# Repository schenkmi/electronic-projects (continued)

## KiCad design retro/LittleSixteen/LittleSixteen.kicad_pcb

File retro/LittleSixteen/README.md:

# LittleSixteen

LittleSixteen is an Open Hardware remake of the Commodore 16, 116 and Plus/4 home computers, featuring many improvements over the original design.

## Summary
While this project started as a simple redrawing of the C16 schematics, it has now evolved into what could be considered the flagship member of the 264 family of Commodore computers, since it has all the characteristics of the other models [^nospeech] and bears a full array of extra features and improvements, while keeping full compatibility with them.

The new goal of this project is to allow anyone to build a very significant home computer from the '80s from scratch, only using parts that can be found on the market [^almost]. The design is fully through-hole so no particular soldering skills are required for the assembly. The estimated cost of ALL materials (case and power supply included) for a single complete machine is around 250-300€.

## Differences and Improvements
The original Commodore 16 was the victim of several cost-cutting measures during its design phase. Its target price was $99 and Commodore still had to have some margin on that, so they really had to spare every cent they could and they went as far as not mounting the decoupling capacitors for a few chips which happened to have another one "close enough". Thus, a further goal of this project was to undo all of those measures and make the design as clean as possible, while also improving on it.

### Modifications introduced in V4
The goal of V4 was to make LittleSixteen an improved Plus/4 clone, rather than a C16 clone.

- 100% Plus/4 compatible User Port.
- 512 kB Hannes-style RAM expansion (which can be reduced to 256 kB through a single jumper for compatibility reasons).
- 2 ROM banks, each of which can carry the whole set of ROMs: KERNAL + BASIC + Function ROMs.
- Onboard SID (either 6581 or 8580 + Optional Digifix) + 3rd joystick port (SID audio is mixed with the TED/Ext audio with configurable volume but direct dedicated output is also available).
- Direct TED audio output connector.
- Joystick swapper.
- Ability to replace keyboard MOS 6529 with 74x273 (so that 6529 can be recycled for User Port, but that one as well can be replaced with a 74x654).
- Removed FB13 in order to reduce luma/chroma crosstalk and improve video quality.
- Pin header with all tape signals (think Internal Tapuino).
- Pin header with all IEC signals (think Internal SD2IEC).

### Modifications introduced in V3
In V3 we started making improvements to the board. The reasoning behind every modification is detailed on the [Development Blog](https://hackaday.io/project/182543-littlesixteen-commodore-16-mainboard), so I'll be pretty terse here.

- Switched to external power regulation, using the C64 power circuit and power supply: drastically reduces the heat inside the case, which is one of the main CPU/TED failure causes.
- Added current-limiting resistors on all ports exposing power pins: this will avoid short-circuiting the power supply, whatever you do on the external connectors.
- Added internal Joystick port buffers: this is basically like having two [OpenC16JoyAdapter](https://github.com/SukkoPera/OpenC16JoyAdapter)s built into the machine, preventing the TED pins to be directly exposed on the joystick ports, which is another common cause of TED failures. It also gives the ports a fixed ground, allowing the use of "advanced" joysticks with autofire functionalities for instance, which require power from the machine.
- Joystick ports now use DB-9 (more properly: DE-9) connectors, just like any other machine of the era: you can now use your favourite C64/Amiga joystick on your C16.
- Similarly, the Datassette port was changed to the C64-style edge connector. An adapter to keep connecting the 1531 Datassette is trivial to make.
- Moved to the C64 power switch, since this can still be found on the market and is functionally equivalent.
- The CPU can now either be an original 7501/8501 or even a 6510, thanks to [Andrew Challis's adapter](http://hackjunk.com/2017/06/23/commodore-16-plus-4-8501-to-6510-cpu-conversion/) being integrated on the board.
- In a similar fashion, the board can either directly accept an original MOS 251641 PLA or [Daniël Mantione's GAL16V8-based reimplementation](https://www.freepascal.org/~daniel/c16pla/).
- The design flaw that prevented the usage of cartridge-based RAM expansions was fixed: you can now plug in an [OpenC16RamExpansion](https://github.com/SukkoPera/OpenC16RamExpansion) without the internal RAM fighting with it.
- Actually that might not even be necessary, as the board now directly supports either 16 or 64 kB of internal RAM.
- Since the RF modulator is basically useless these days, a [replacement circuit](https://github.com/mbarszcz-pcb/c64-rf-modulator-replacement) was integrated on the board, providing either Luma+Chroma (say S-Video) or Composite Video.
- Added the possibility of combining the KERNAL and BASIC in a single all-in-one ROM: this allows replacing the original power-hungry chips with a single W27C512, which can also incorporate the Plus/4 function ROMs.
- ESD protection was improved on all ports.
- The track and ground plane layout were optimized in a few places in order to reduce noise and crosstalk.

While the comprehensive switch of connectors to the C64 counterparts might be frowned upon, it was done because [C64-style cases](https://icomp.de/shop-icomp/en/shop/product/c64c-case.html) are still in production and this way LittleSixteen V3 will fit them just perfectly, yielding the ability to build new C16s from scratch, which is another one of our goals.

### Modifications introduced in V2
V2 was meant to be a 1:1 copy of the original board with some essential improvements requiring minimum effort. The goal was to have a proved-working design we could start from in order to make improvements.

- The original board was probably laid out by hand and a lot of tracks were drawn with arbitrary slopes. I have sticked to only 45 degrees tracks, which of course means I could not follow the original tracks exactly, but I tried to stay as close to them as possible and to keep all the "visual hints" that allow identifying a track quickly. I must admit I'm quite satisfied of the end result, to be honest.
- I used my usual track widths and via sizes (plus some new values for the larger tracks), I didn't bother figuring out what sizes the original board used.
- All tracks were laid out "by eye", which means with *reasonable* - not *maniacal* - accuracy to the original design. Most care was taken in the positioning of components that ought to be in a certain position (i.e.: screw holes and I/O connectors), to ensure drop-in replaceability. Other components and tracks are "more or less" there, but as the board was wholly laid out from scratch by hand, don't expect sub-millimeter accuracy.
- The footprints for all DIP chips use "long pads". This makes them easier to solder and more solid to the board should you need to rework them. This forced a few tracks running very close to the original pads to be slightly offset away.
- Some footprints are slightly longer/larger/wider pitch/whatever than the originals, so that I could use ready-made KiCad libraries.
- Footprints for the connectors and modulator were taken from [StormTrooper's Plus/4 remake](https://github.com/StormTrooper/Commodore-Plus4), without checking them for correctness.
- I didn't bother to create the right footprint for the original power connector, as there's no point in wasting time for some item that is nowhere to be found these days. I used a much more common one instead. Same goes for the inductor.
- I didn't pay much attention to the silkscreen, many labels can probably be placed better, but I added a description for every IC, like it or not.
- Proper footprints were added for all the protection diodes that Commodore forcibly retrofitted on real boards (See D96-99).
- With the C16, Commodore went as far as saving a few cents by not mounting the decoupling capacitors for a few chips. They left the pads on the board but removed all silkscreen indications. These were restored and assigned random numbers.
- The ground fill is autogenerated by KiCad, so it won't match the original exactly (not even close).
- Probably there's something more I've forgotten.

If you don't like any of the above, feel free to fix it yourself and [submit a Pull Request](https://github.com/SukkoPera/LittleSixteen/pulls).

## Testing
V3  and V4 of the board were throughly tested by project collaborator Edoardo Auteri, as you can read on the [Development Blog](https://hackaday.io/project/182543/log/202804-how-to-make-the-changes-that-change-everything). In his words:

> The machine works flawlessly providing superior audio and video performance, low power consumption and compatibility with the 1530 Datassette Unit (C2N model), SD2IEC, Atari joysticks and pads.

## Assembly
If you want to build your own board, **please make sure read the assembly notes on [the Wiki](https://github.com/SukkoPera/LittleSixteen/wiki) carefully!**

Note that there are different pages for different revisions of the board.

## Releases
If you want to get this board produced, you are recommended to get [the latest release](https://github.com/SukkoPera/LittleSixteen/releases) rather than the current git version, as the latter might be under development and is not guaranteed to be working.

Every release is accompanied by its Bill Of Materials (BOM) file and any relevant notes about it, which you are recommended to read carefully.

**I am not providing ready-to-use gerber files**. If all you want is **to get boards made, I would really appreciate if you did so [in a way that supports the project](#support-the-project)**.

## License
The LittleSixteen documentation, including the design itself, is copyright &copy; SukkoPera 2019-2025 and is licensed under the [Creative Commons Attribution-NonCommercial-ShareAlike 4.0 International License](https://creativecommons.org/licenses/by-nc-sa/4.0/).

This documentation is distributed *as is* and WITHOUT ANY EXPRESS OR IMPLIED WARRANTIES whatsoever with respect to its functionality, operability or use, including, without limitation, any implied warranties OF MERCHANTABILITY, SATISFACTORY QUALITY, FITNESS FOR A PARTICULAR PURPOSE or infringement. We expressly disclaim any liability whatsoever for any direct, indirect, consequential, incidental or special damages, including, without limitation, lost revenues, lost profits, losses resulting from business interruption or loss of data, regardless of the form of action or legal theory under which the liability may be asserted, even if advised of the possibility or likelihood of such damages.

## Support the Project
If you want to get some boards manufactured, you can get them from PCBWay through this link:

You get my gratitude and cheap, professionally-made and good quality PCBs, I get some credit that will help with this and [other projects](https://www.pcbway.com/project/member/shareproject/?bmbid=41100). You won't even have to worry about the various PCB options, it's all pre-configured for you!

Also, if you still have to register, [you can use this link](https://www.pcbway.com/setinvite.aspx?inviteid=41100) to get some bonus initial credit (and yield me some more).

You can also buy me a coffee if you want:

## Thanks
- My father, for buying me my C16 when I was 8, my first computer ever. This project is dedicated to his memory.
- Amiwell, for giving me a free C16 that I used to trace a lot of connections.
- [StormTrooper](https://github.com/StormTrooper/Commodore-Plus4) for his similar project about the Plus/4, which is where many of the footprints and 3D models used in this project come from.
- J. F. Gomez, for the [3D model of the Barrel jack](https://grabcad.com/library/dc-power-jack-5-5mm-x-2-1mm-2-54mm-pitch-1).
- [Edoardo Auteri](https://github.com/kinmami), for his invaluable advice on analog stuff and for fully assembling the first prototype and testing it thoroughly.
- Gordon Fecyk AKA Great White Retro, for beta-testing, making videos of his builds and spreading the word.
- Last but not least, thanks to [PCBWay](https://www.pcbway.com) for sponsoring the project and providing us with free prototypes of V3.

[^nospeech]: Ok, ok... No V364 speech support, I'll admit!
[^almost]: Almost, the CPU, TED and Expansion port connector must be recovered somehow.

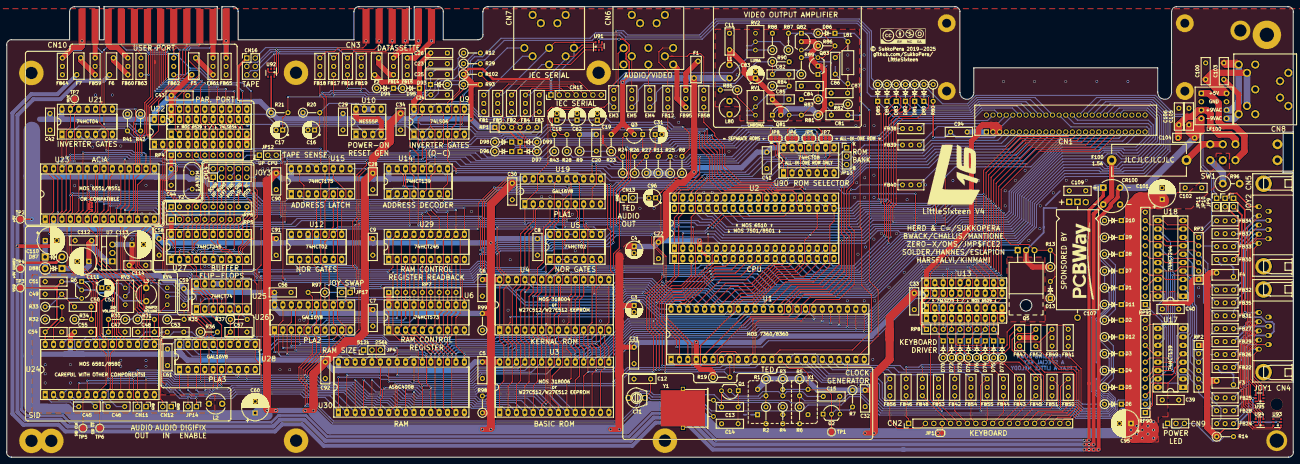
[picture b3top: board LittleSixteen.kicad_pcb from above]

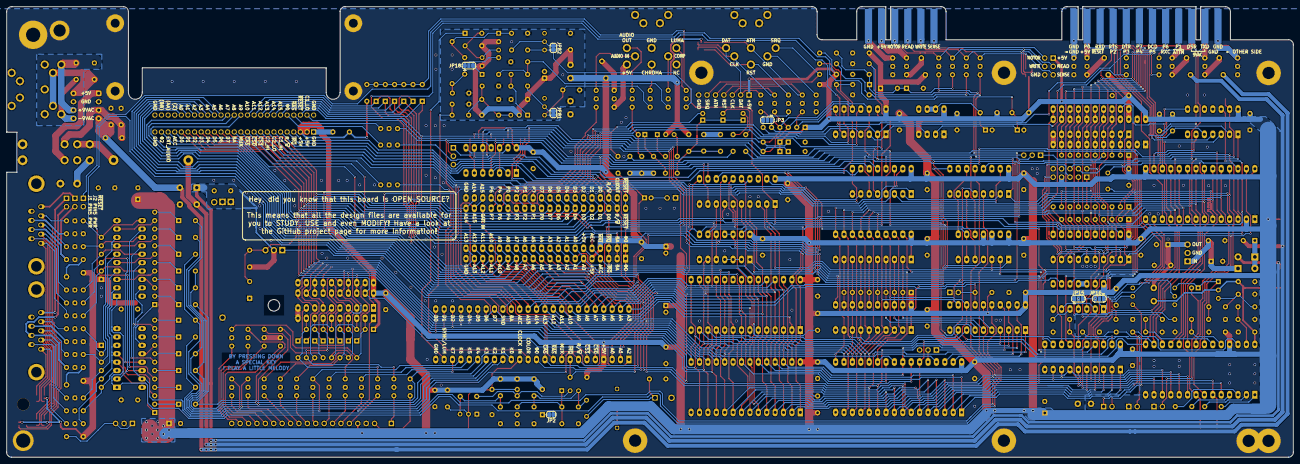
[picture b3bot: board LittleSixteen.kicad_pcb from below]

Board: 2 copper layers, 389.0 x 136.2 mm, 364 parts (7 on the bottom side), 346 nets.

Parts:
C3, C4, C16, C18, C19, C31, C52, C62, C83, C96: 10u/25V; CP_Radial_D5.0mm_P2.00mm
C5, C6, C7, C8, C9, C11, C21, C22, C26, C28, C29, C30, C33, C34, C39, C40, C41, C42, C43, C44, C51, C53, C54, C55, C56, C58, C59, C61, C85, C90, C91, C92, C94, C100, C102, C109, C112, C114: 100n; C_Disc_D8.0mm_W2.5mm_P5.00mm
C12: 22p; C_Disc_D8.0mm_W2.5mm_P5.00mm
C13, C86: 220p; C_Disc_D8.0mm_W2.5mm_P5.00mm
C14, C82: 150p; C_Disc_D8.0mm_W2.5mm_P5.00mm
C15, C20: 10n; C_Disc_D8.0mm_W2.5mm_P5.00mm
C17: 1u/16V; CP_Radial_D5.0mm_P2.00mm
C23, C24, C25, C50, C57: 470p; C_Disc_D8.0mm_W2.5mm_P5.00mm
C32, C84: 100p; C_Disc_D8.0mm_W2.5mm_P5.00mm
C45, C46: 22n; C_Disc_D8.0mm_W2.5mm_P5.00mm
C47, C48: 2.2n; C_Disc_D8.0mm_W2.5mm_P5.00mm
C49: 1n; C_Disc_D8.0mm_W2.5mm_P5.00mm
C60, C95, C101, C110, C111, C113: 470u/25V; CP_Radial_D8.0mm_P3.50mm
C81, C87: 330p; C_Disc_D8.0mm_W2.5mm_P5.00mm
C103, C104, C105, C106: 220n/25V; C_Disc_D8.0mm_W2.5mm_P5.00mm
C107: 2200u/25V; Axial_Cap_Dual
CN1: EXPANSION_CONNECTOR; 50Pin_Edge_Connector
CN2: KEYBOARD_HEADER; PinHeader_1x20_P2.54mm_NoPin2
CN4: JOY1; DB_9M
CN5: JOY2; DB_9M
CN6: AUDIO_VIDEO; DIN-8_DS_8_102_OR_102B
CN7: SERIAL_BUS; DIN-6_DS_6_102_OR_102B
CN8: POWER_INPUT; DIN-7_DS_7_102_OR_102B
CN9: LED_CONNECTOR; PinHeader_1x03_P2.54mm_Vertical
CN10: USERPORT; Plus4_UserPort
CN11: CONN_SID_OUTPUT; PinHeader_1x02_P2.54mm_Vertical
CN12: CONN_SID_INPUT; PinHeader_1x02_P2.54mm_Vertical
CN13: CONN_TED_OUTPUT; PinHeader_1x02_P2.54mm_Vertical
CN14: CONN_JOY3; PinHeader_2x05_P2.54mm_Vertical
CN15: CONN_IEC_INT; PinHeader_1x07_P2.54mm_Vertical
CN16: CONN_TAPE_INT; PinHeader_2x03_P2.54mm_Vertical
CN93: C64_STYLE_CASSETTE; C64-Cassette-Port-Male
CR100: NTE5304; Diode_Bridge_Round_D9.8mm
CT1: 40p; VariCap
D1, D2, D3, D4, D5, D6, D7, D8, D9, D10, D11, D12, D70, D71, D72, D73, D74, D75, D76, D77, D80, D81, D82, D83, D84, D85, D86, D93, D94, D95, D96, D97, D98, D99: 1n4148; D_DO-35_SOD27_P5.08mm_Vertical_KathodeUp
D13: 6.8V; D_DO-35_SOD27_P5.08mm_Vertical_KathodeUp_Zener
D87, D88: 1n4001; D_DO-41_SOD81_P5.08mm_Vertical_KathodeUp
EM3, EM4, EM5: 270p; EMI_Filter
F1, F2, F5: 250m; Fuse_Bourns
F3, F4, F6, F7: 400m; Fuse_Bourns
F100: 1.5A; Fuseholder_Cylinder-5x20mm_Stelvio-Kontek_PTF78_Horizontal_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
FB1, FB2, FB3, FB4, FB5, FB12, FB14, FB15, FB16, FB17, FB18, FB19, FB22, FB24, FB25, FB26, FB27, FB28, FB29, FB30, FB31, FB32, FB33, FB34, FB35, FB37, FB41, FB42, FB43, FB44, FB45, FB46, FB47, FB48, FB49, FB50, FB51, FB52, FB53, FB54, FB55, FB56, FB58, FB59, FB60, FB61, FB62, FB63, FB64, FB65, FB95: FERRITE; EMI_Filter
FB38, FB39, FB40: DO NOT MOUNT; EMI_Filter
H1, H2, H3, H4, H6, H7, H15, H16, H17: MountingHole_Pad; MountingHole_3.7mm_Pad
H9, H10: MountingHole_Pad; MountingHole_4.3mm_M4_Pad
H11, H12, H13, H14: MountingHole_Pad; MountingHole_2.7mm_Pad
JP1: JMP_KBD_POWER; SolderJumper-2_P1.3mm_Open_RoundedPad1.0x1.5mm
JP2: JMP_OSC_GND; SolderJumper-2_P1.3mm_Open_RoundedPad1.0x1.5mm
JP3: JP_IECRST; SolderJumper-3_P1.3mm_Open_RoundedPad1.0x1.5mm
JP4: SW_RAMSIZE; PinHeader_1x03_P2.54mm_Vertical
JP5: SW_KCE; SolderJumper-3_P1.3mm_Open_RoundedPad1.0x1.5mm
JP6: SW_KA15; SolderJumper-3_P1.3mm_Open_RoundedPad1.0x1.5mm
JP7: SW_KA14; SolderJumper-3_P1.3mm_Open_RoundedPad1.0x1.5mm
JP8: SW_BCE; SolderJumper-3_P1.3mm_Open_RoundedPad1.0x1.5mm
JP9: JMP_J1_POW5; PinHeader_1x02_P2.54mm_Vertical
JP10: JMP_J2_POW5; PinHeader_1x02_P2.54mm_Vertical
JP11: SW_RESET; PinHeader_1x02_P2.54mm_Vertical
JP12: JMP_TPSENSE; PinHeader_1x03_P2.54mm_Vertical
JP13: SW_ROM_BANK; PinHeader_1x03_P2.54mm_Vertical
JP14: SW_DIGIFIX; PinHeader_1x02_P2.54mm_Vertical
JP15: JMP_SIDCLK_SET; SolderJumper-3_P1.3mm_Open_RoundedPad1.0x1.5mm
JP16: JMP_SIDCLK_RST; SolderJumper-3_P1.3mm_Open_RoundedPad1.0x1.5mm
JP17: SW_JOYSWAP; PinHeader_1x02_P2.54mm_Vertical
JP18: JMP_COMP_VIDEO; SolderJumper-3_P1.3mm_Open_RoundedPad1.0x1.5mm
JP81: JMP_RV1_BYPASS; SolderJumper-2_P1.3mm_Open_RoundedPad1.0x1.5mm
JP82: JMP_RV2_BYPASS; SolderJumper-2_P1.3mm_Open_RoundedPad1.0x1.5mm
L1, L2, L3, L80: FERRITE; L_Radial_D6.0mm_P4.00mm
L81: 10u; L_Axial_L7.0mm_D3.3mm_P12.70mm_Horizontal_Fastron_MICC
LF100: CM4545Z131B-10
Q1, Q2, Q3, Q6, Q81, Q82, Q83: 2SC1815; TO-92_Inline_Wide
Q5: 2SD880; TO-220-3_Horizontal_TabUp
R1, R23, R33, R41, R42, R97, R98, R99: 10k; R_Axial_DIN0207_L6.3mm_D2.5mm_P5.08mm_Vertical
R2: 4.7k; R_Axial_DIN0207_L6.3mm_D2.5mm_P5.08mm_Vertical
R3, R7, R13, R14: 470; R_Axial_DIN0207_L6.3mm_D2.5mm_P5.08mm_Vertical
R4, R37: 220; R_Axial_DIN0207_L6.3mm_D2.5mm_P5.08mm_Vertical
R5: 18k; R_Axial_DIN0207_L6.3mm_D2.5mm_P5.08mm_Vertical
R6: 1.5k; R_Axial_DIN0207_L6.3mm_D2.5mm_P5.08mm_Vertical
R8, R24, R28, R32, R34, R43, R82, R86: 1k; R_Axial_DIN0207_L6.3mm_D2.5mm_P5.08mm_Vertical
R9: 12k; R_Axial_DIN0207_L6.3mm_D2.5mm_P5.08mm_Vertical
R11, R21, R25, R36: 100k; R_Axial_DIN0207_L6.3mm_D2.5mm_P5.08mm_Vertical
R12, R19, R81, R93: 3.3k; R_Axial_DIN0207_L6.3mm_D2.5mm_P5.08mm_Vertical
R20: 47k; R_Axial_DIN0207_L6.3mm_D2.5mm_P5.08mm_Vertical
R26, R27: 240; R_Axial_DIN0207_L6.3mm_D2.5mm_P5.08mm_Vertical
R29, R30, R31, R89: 100; R_Axial_DIN0207_L6.3mm_D2.5mm_P5.08mm_Vertical
R35: 180k; R_Axial_DIN0207_L6.3mm_D2.5mm_P5.08mm_Vertical
R80, R83: 5.6k; R_Axial_DIN0207_L6.3mm_D2.5mm_P5.08mm_Vertical
R84: 33; R_Axial_DIN0207_L6.3mm_D2.5mm_P5.08mm_Vertical
R85, R87, R88, R90: 150; R_Axial_DIN0207_L6.3mm_D2.5mm_P5.08mm_Vertical
R96: 10 2.5W; R_Axial_DIN0414_L11.9mm_D4.5mm_P5.08mm_Vertical
R102: 330; R_Axial_DIN0207_L6.3mm_D2.5mm_P5.08mm_Vertical
RP1: 1k; R_Array_SIP6
RP2, RP3: 3.3k; R_Array_SIP6
RP4: 3.3k; R_Array_SIP9
RP5, RP8: 4.7k; R_Array_SIP9
RP6: 100; R_Array_SIP10
RP7: 10k; R_Array_SIP9
RP90, RP91: 100; R_Array_SIP12
RV1: 1k; Potentiometer_Bourns_3296W_Vertical
RV2: 220; Potentiometer_Bourns_3296W_Vertical
RV3: 10k; Potentiometer_Bourns_3296W_Vertical
RV4: 1M; Potentiometer_Bourns_3296W_Vertical
SW1: SW_POWER; C64_PowerSwitch
TP1: CLOCK_TESTPOINT; TestPoint_Pad_D2.0mm
TP2: FIVEV_TESTPOINT; TestPoint_Pad_D2.0mm
TP3: VSID_TESTPOINT; TestPoint_Pad_D2.0mm
TP4: NINEV_TESTPOINT; TestPoint_Pad_D2.0mm
TP5: SIDCLK_TESTPOINT; TestPoint_Pad_D2.0mm
TP6: SIDCS_TESTPOINT; TestPoint_Pad_D2.0mm
TP7: MUX_TESTPOINT; TestPoint_Pad_D2.0mm
U1: MOS_7360_TED; DIP-48_W15.24mm_Socket_LongPads
U2: MOS_8501; DIP-40_W15.24mm_Socket_LongPads
U3: 23128_BASIC; DIP-28_W15.24mm_Socket_LongPads
U4: 23128_KERNAL; DIP-28_W15.24mm_Socket_LongPads
U5, U12: 74HCT02; DIP-14_W7.62mm_Socket_LongPads
U6: 74HCT573; DIP-20_W7.62mm_Socket_LongPads
U7: L7812; TO-220-3_Vertical
U9: 74LS06; DIP-14_W7.62mm_Socket_LongPads
U10: NE555P; DIP-8_W7.62mm_Socket_LongPads
U13, U22: MOS_6529; DIP-20_W7.62mm_Socket_LongPads
U14, U17: 74HCT139; DIP-16_W7.62mm_Socket_LongPads
U15: 74HCT175; DIP-16_W7.62mm_Socket_LongPads
U18: 74HCT244; DIP-20_W7.62mm_Socket_LongPads
U19, U26, U28: GAL16V8; DIP-20_W7.62mm_Socket_LongPads
U20: 74HCT273; DIP-20_W7.62mm_Socket_LongPads
U21: 74HCT04; DIP-14_W7.62mm_Socket_LongPads
U23: MOS_6551_ACIA; DIP-28_W15.24mm_Socket_LongPads
U24: MOS_8580; DIP-28_W15.24mm_Socket_LongPads
U25: 74HCT74; DIP-14_W7.62mm_Socket_LongPads
U27, U29: 74HCT245; DIP-20_W7.62mm_Socket_LongPads
U30: AS6C4008; DIP-32_W15.24mm_Socket_LongPads
U90: 74HCT08; DIP-14_W7.62mm_Socket_LongPads
U91, U92, U93, U94, U95: DT1042; TSOP-6_1.65x3.05mm_P0.95mm
U102: MOS_6510; DIP-40_W15.24mm_Socket_LongPads
U122: 74LS654; DIP-24_W7.62mm_Socket_LongPads
V0: LOGO; Logo
V1: PCBWAY_LOGO; pcbway
V2: CC BY-NC-SA 4.0; cc_by_nc_sa
X1: OSC_DIP14; Oscillator_DIP-8+14
Y1: 17.734475M; Crystal_HC49-U_Horizontal_1EP_style2
Y2: 1.8432M; Crystal_HC49-U_Vertical

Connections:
+9V: C107.1, C109.1, CR100.1, D87.2, Q5.2, R13.1, TP4.1
+9VAC: C110.2, CR100.2, F6.1, F100.1
-9VAC: C104.2, C105.1, CR100.4, F7.1, LF100.4
/Datassette & Serial Bus/iec_atn: CN7.3, CN15.5, FB5.1, U91.6
/Datassette & Serial Bus/iec_clk: CN7.4, CN15.3, FB4.1, U91.3
/Datassette & Serial Bus/iec_dat: CN7.5, CN15.2, FB3.1, U91.4
/Datassette & Serial Bus/iec_rst: CN7.6, CN15.4, FB2.1, U91.1
/Datassette & Serial Bus/iec_srq: CN7.1, CN15.6, R102.2
/Datassette & Serial Bus/tape_+5v: CN93.2, FB14.1
/Datassette & Serial Bus/tape_gnd: CN93.1, FB15.1
/Datassette & Serial Bus/tape_mtr: CN16.2, CN93.3, FB19.1
/Datassette & Serial Bus/tape_mtr2: FB19.2, Q5.1
/Datassette & Serial Bus/tape_read: CN16.3, CN93.4, FB16.1, U92.3
/Datassette & Serial Bus/tape_sense: CN16.5, CN93.6, FB18.1, U92.1
/Datassette & Serial Bus/tape_wr: CN16.4, CN93.5, FB17.1, U92.6
/Datassette & Serial Bus/tape_wr2: C24.2, FB17.2, R29.1
/Datassette & Serial Bus/~p3: D13.2, Q5.3, R13.2, U9.6
/Joysticks/1d: FB25.1, RP2.4, U18.4
/Joysticks/1f: FB28.1, RP2.6, U17.3
/Joysticks/1l: FB26.1, RP2.3, U18.6
/Joysticks/1r: FB27.1, RP2.2, U18.8
/Joysticks/1u: FB24.1, RP2.5, U18.2
/Joysticks/2d: FB32.1, RP3.4, U18.15
/Joysticks/2f: FB35.1, RP3.3, U17.13
/Joysticks/2l: FB33.1, RP3.5, U18.13
/Joysticks/2r: FB34.1, RP3.6, U18.11
/Joysticks/2u: FB31.1, RP3.2, U18.17
/Joysticks/b1d: RP90.11, U18.16
/Joysticks/b1l: RP90.7, U18.14
/Joysticks/b1r: RP90.5, U18.12
/Joysticks/b1u: RP91.3, U18.18
/Joysticks/b2d: RP91.7, U18.5
/Joysticks/b2l: RP91.9, U18.7
/Joysticks/b2r: RP91.11, U18.9
/Joysticks/b2u: RP91.5, U18.3
/Joysticks/f1d: CN4.2, FB25.2, U95.6
/Joysticks/f1f: CN4.6, FB28.2, U95.1
/Joysticks/f1l: CN4.3, FB26.2, U95.4
/Joysticks/f1r: CN4.4, FB27.2, U94.3
/Joysticks/f1u: CN4.1, FB24.2, U95.3
/Joysticks/f2d: CN5.2, FB32.2, U94.4
/Joysticks/f2f: CN5.6, FB35.2, U94.6
/Joysticks/f2l: CN5.3, FB33.2, U93.3
/Joysticks/f2r: CN5.4, FB34.2, U93.4
/Joysticks/f2u: CN5.1, FB31.2, U94.1
/PLA & Chip Selection/addr_clk: U12.2, U19.16
/PLA & Chip Selection/rom_switch: U12.6, U12.9, U19.19
/Power & Misc/in_+5v: C100.1, CN8.4, CN8.5, LF100.8
/Power & Misc/in_+9avc: C103.1, CN8.7, LF100.5
/Power & Misc/in_-9vac: C103.2, CN8.6, LF100.6
/Power & Misc/in_gnd: C100.2, CN8.1, CN8.2, CN8.3, LF100.7
/RAM/a16: U26.19, U30.31
/RAM/a17: U26.18, U30.30
/RAM/a18: JP4.2, U30.28
/RAM/a18_from_pla: JP4.1, U26.17
/RAM/sram_ce: U5.1, U30.22, U30.24
/RAM/~cs_ramwr: U5.13, U25.13
/RAM/~u3enable: U6.1, U25.9
/ROMs/rom_a14: JP7.2, U3.27, U4.27
/ROMs/rom_a15: JP6.2, U3.1, U4.1
/ROMs/singlerom_a14: JP7.3, U90.6
/ROMs/singlerom_a15: JP6.3, U90.3, U90.12
/ROMs/singlerom_ce: JP13.2, U90.11
/ROMs/singlerom_ce_bas: JP8.3, JP13.3
/ROMs/singlerom_ce_krn: JP5.3, JP13.1
/ROMs/~ce_basic_rom: JP8.2, R98.2, U3.22
/ROMs/~ce_krn_rom: JP5.2, R99.1, U4.22
/ROMs/~cef: U90.8, U90.13
/SID!/audio_in: C53.2, JP14.1, U24.26
/SID!/audio_out: R32.2, R33.2, U24.27
/SID!/down: CN14.2, RP6.4
/SID!/fire: CN14.6, RP6.9
/SID!/left: CN14.3, RP6.7
/SID!/potx: CN14.9, R30.1
/SID!/poty: CN14.5, R31.1
/SID!/right: CN14.4, RP6.2
/SID!/sidclk: C57.1, R37.1, TP5.1, U24.6
/SID!/up: CN14.1, RP6.6
/SID!/~mux: U21.12, U25.3
/TED/clock_in: Q2.2, R7.2, TP1.1, U1.14, X1.8
/User Port/cba: U28.15, U122.23
/User Port/dcd_ttl: CN10.H, R41.2, U21.5
/User Port/dsr_ttl: CN10.L, R42.2, U21.9
/User Port/dtr_ttl: CN10.E, U21.4
/User Port/gab: U28.14, U122.3
/User Port/p0: CN10.B, RP4.2, U22.2, U122.4
/User Port/p1: CN10.K, RP4.3, U22.3, U122.5
/User Port/p3: CN10.5, RP4.5, U22.5, U122.7
/User Port/p4: CN10.6, RP4.6, U22.6, U122.8
/User Port/p5: CN10.7, RP4.7, U22.7, U122.9
/User Port/p6: CN10.J, RP4.8, U22.8, U122.10
/User Port/p7: CN10.F, RP4.9, U22.9, U122.11
/User Port/q+: U23.6, Y2.2
/User Port/q-: U23.7, Y2.1
/User Port/rts_ttl: CN10.D, U21.2
/User Port/rxc_ttl: CN10.8, U23.5
/User Port/rxd_ttl: CN10.C, U23.12
/User Port/txd_ttl: CN10.M, U23.10
/User Port/~dcd_ttl: U21.6, U23.16
/User Port/~dsr_ttl: U21.8, U23.17
/User Port/~dtr_ttl: U21.3, U23.11
/User Port/~rts_ttl: U21.1, U23.8
A15_10_HIGH: D80.2, D81.2, D82.2, D83.2, D84.2, D85.2, R80.1, U19.1, U28.19
AEC: CN1.22, U1.35, U2.4, U26.11, U102.5
AGND: C47.2, C48.2, C49.2, C51.1, C54.2, C55.2, CN11.1, CN12.1, L2.2, R32.1, R34.1, R35.1, R36.1, RV3.1, U24.14
BA: CN1.13, U1.34, U2.2, U102.2
C1_HIGH: CN1.6, U14.10
C1_LOW: CN1.B, U14.6
C2_HIGH: CN1.8, U14.9
C2_LOW: CN1.7, U14.7
COLOR: C81.2, R82.1, U1.13
COLOR_CV_PICKUP: C82.2, Q81.1, R84.2
COLOR_OUT: EM4.2, JP81.2, R85.1, RV1.3
COMP_OUT: C82.1, EM5.2, R89.1, R90.1
CS_RAMWR: U5.11, U5.12, U6.11, U28.16
EXT_AUDIO: CN1.23, FB58.2, R25.2, R28.1
GND: C3.2, C4.2, C5.2, C6.2, C7.2, C8.2, C9.1, C12.2, C14.2, C16.2, C17.2, C20.2, C21.2, C22.2, C23.1, C24.1, C25.1, C26.1, C28.2, C29.2, C30.2, C32.2, C33.2, C34.2, C39.2, C40.2, C41.2, C42.2, C43.2, C44.2, C56.2, C57.2, C58.2, C59.2, C60.2, C61.2, C90.2, C91.2, C92.2, C94.2, C95.2, C101.2, C102.2, C105.2, C106.2, C107.2, C109.2, C111.2, C112.2, C113.2, C114.2, CN1.1, CN1.25, CN1.A, CN1.CC, CN2.4, CN4.0, CN5.0, CN6.0, CN6.2, CN7.0, CN8.0, CN9.2, CN13.1, CN14.8, CN15.7, CN16.6, CR100.3, CT1.2, D13.1, D94.2, D96.2, D98.2, EM3.3, EM4.3, EM5.3, FB1.2, FB1.3, FB2.3, FB3.3, FB4.3, FB5.3, FB12.3, FB14.3, FB15.2, FB15.3, FB16.3, FB17.3, FB18.3, FB19.3, FB22.3, FB24.3, FB25.3, FB26.3, FB27.3, FB28.3, FB29.1, FB29.3, FB30.3, FB31.3, FB32.3, FB33.3, FB34.3, FB35.3, FB37.1, FB37.3, FB38.3, FB39.3, FB40.3, FB41.3, FB42.3, FB43.3, FB44.3, FB45.3, FB46.3, FB47.3, FB48.3, FB49.3, FB50.3, FB51.3, FB52.3, FB53.3, FB54.3, FB55.3, FB56.3, FB58.3, FB59.3, FB60.3, FB61.3, FB62.3, FB63.3, FB64.2, FB64.3, FB65.2, FB65.3, FB95.3, H1.1, H2.1, H3.1, H4.1, H6.1, H7.1, H9.1, H10.1, H11.1, H12.1, H13.1, H14.1, H15.1, H16.1, H17.1, JP2.1, JP4.3, JP11.2, JP17.1, L2.1, L80.1, LF100.2, Q2.1, R2.2, R4.2, R6.2, R9.2, R11.1, R25.1, R27.1, R96.2, SW1.0, U1.24, U2.20, U3.14, U3.20, U4.14, U4.20, U5.7, U6.10, U7.2, U9.7, U10.1, U12.7, U13.10, U14.8, U15.8, U17.8, U18.10, U19.10, U20.10, U21.7, U22.10, U23.1, U23.9, U25.7, U25.11, U25.12, U26.10, U27.10, U28.10, U29.10, U30.16, U90.7, U91.2, U92.2, U93.2, U94.2, U95.2, U102.21, U122.1, U122.2, U122.12, U122.21, X1.7, Y1.3
KEYPORT_CS: U13.19, U19.17, U20.11
LUMA_CV_PICKUP: JP18.2, R89.2
LUM_OUT: EM3.2, JP82.2, R88.1, RV2.3
MUX: CN1.12, TP7.1, U1.9, U2.23, U19.7, U21.13
unnamed: C12.1, CT1.1, Y1.2
unnamed: C13.1, Q1.3, R1.2, R2.1, Y1.1
unnamed: C13.2, C14.1, Q1.1, R4.1
unnamed: C15.1, Q2.3, R5.2, R6.1
unnamed: C15.2, Q1.2, R3.2
unnamed: C16.1, R20.2, U10.6, U10.7
unnamed: C17.1, JP11.1, R21.2, U10.2
unnamed: C18.1, C19.1, C20.1, C62.1, R9.1, R23.1, R24.1
unnamed: C18.2, R28.2
unnamed: C19.2, R8.2
unnamed: C25.2, D93.1, FB18.2, JP12.2, R12.1
unnamed: C31.1, R26.1, R27.2
unnamed: C31.2, FB12.2, R11.2
unnamed: C45.1, U24.1
unnamed: C45.2, U24.2
unnamed: C46.1, U24.3
unnamed: C46.2, U24.4
unnamed: C47.1, R30.2, U24.24
unnamed: C48.1, R31.2, U24.23
unnamed: C49.1, C50.2, Q6.3, R33.1
unnamed: C50.1, C52.1, Q6.1, R34.2, RV3.3
unnamed: C52.2, CN11.2
unnamed: C53.1, CN12.2, R36.2
unnamed: C62.2, R43.2
unnamed: C81.1, C84.2, Q81.3, R81.2, R83.1
unnamed: C86.1, C87.2, JP18.1, L81.2
unnamed: C86.2, L81.1, Q82.1, R87.2
unnamed: C96.2, CN13.2
unnamed: C104.1, C106.1, LF100.3, SW1.4
unnamed: C110.1, D87.1, D88.2
unnamed: C111.1, C112.1, D88.1, U7.1
unnamed: C113.1, C114.1, L3.1, U7.3
unnamed: CN1.11, FB40.2
unnamed: CN1.D, FB38.2
unnamed: CN1.E, FB39.2
unnamed: CN2.1, FB46.2
unnamed: CN2.3, FB56.2
unnamed: CN2.5, JP1.2
unnamed: CN2.6, FB48.2
unnamed: CN2.7, FB53.2
unnamed: CN2.8, FB42.2
unnamed: CN2.9, FB54.2
unnamed: CN2.10, FB55.2
unnamed: CN2.11, FB44.2
unnamed: CN2.12, FB43.2
unnamed: CN2.13, FB45.2
unnamed: CN2.14, FB51.2
unnamed: CN2.15, FB50.2
unnamed: CN2.16, FB47.2
unnamed: CN2.17, FB52.2
unnamed: CN2.18, FB49.2
unnamed: CN2.19, FB41.2
unnamed: CN4.5, JP9.1
unnamed: CN4.7, FB22.2, JP9.2
unnamed: CN4.8, FB29.2
unnamed: CN5.5, JP10.1
unnamed: CN5.7, FB30.2, JP10.2
unnamed: CN5.8, FB37.2
unnamed: CN6.1, EM3.1
unnamed: CN6.3, FB12.1
unnamed: CN6.4, EM5.1
unnamed: CN6.5, FB58.1
unnamed: CN6.6, EM4.1
unnamed: CN6.8, FB95.2
unnamed: CN7.2, FB1.1
unnamed: CN9.1, CN9.3, R14.2
unnamed: CN10.1, CN10.A, FB65.1
unnamed: CN10.2, FB61.1
unnamed: CN10.3, FB62.1
unnamed: CN10.9, FB63.1
unnamed: CN10.10, FB60.1
unnamed: CN10.11, FB59.1
unnamed: CN10.12, CN10.N, FB64.1
unnamed: D1.1, RP91.4
unnamed: D2.1, RP90.12
unnamed: D3.1, RP90.8
unnamed: D4.1, RP90.6
unnamed: D5.1, RP90.4
unnamed: D6.1, RP90.2
unnamed: D7.1, RP91.6
unnamed: D8.1, RP91.8
unnamed: D9.1, RP91.10
unnamed: D10.1, RP91.12
unnamed: D11.1, RP91.2
unnamed: D12.1, RP90.10
unnamed: D70.1, U20.19
unnamed: D70.2, FB41.1, RP8.2, U13.2
unnamed: D71.1, U20.16
unnamed: D71.2, FB42.1, RP8.3, U13.3
unnamed: D72.1, U20.2
unnamed: D72.2, FB43.1, RP8.4, U13.4
unnamed: D73.1, U20.5
unnamed: D73.2, FB44.1, RP8.5, U13.5
unnamed: D74.1, U20.15
unnamed: D74.2, FB45.1, RP8.6, U13.6
unnamed: D75.1, U20.12
unnamed: D75.2, FB46.1, RP8.7, U13.7
unnamed: D76.1, U20.6
unnamed: D76.2, FB47.1, RP8.8, U13.8
unnamed: D77.1, U20.9
unnamed: D77.2, FB48.1, RP8.9, U13.9
unnamed: D86.2, Q82.3, Q83.3, R86.2
unnamed: F1.2, FB95.1
unnamed: F2.2, FB14.2
unnamed: F3.2, FB22.1
unnamed: F4.2, FB30.1
unnamed: F5.2, FB61.2
unnamed: F6.2, FB60.2
unnamed: F7.2, FB59.2
unnamed: F100.2, SW1.5, SW1.6
unnamed: FB2.2, JP3.2
unnamed: JP2.2, X1.1
unnamed: JP3.3, RP1.6, U9.4
unnamed: JP14.2, RV4.1
unnamed: JP15.2, U25.4
unnamed: JP16.2, U25.1
unnamed: JP18.3, Q83.1
unnamed: JP81.1, R84.1, RV1.2
unnamed: JP82.1, R87.1, RV2.2
unnamed: LF100.1, SW1.1
unnamed: Q3.1, R26.2
unnamed: Q3.3, R24.2
unnamed: R35.2, RV4.2
unnamed: R37.2, U25.5
unnamed: R96.1, SW1.3
unnamed: RP5.2, RP6.1, U27.5
unnamed: RP5.3, RP6.3, U27.3
unnamed: RP5.4, U27.7
unnamed: RP5.5, RP6.5, U27.2
unnamed: RP5.6, U27.8
unnamed: RP5.7, U27.9
unnamed: RP5.8, RP6.8, U27.4
unnamed: RP5.9, RP6.10, U27.6
unnamed: RP90.1, U17.4
unnamed: RP90.3, U17.5
unnamed: RP90.9, U17.12
unnamed: RP91.1, U17.11
unnamed: U5.2, U5.3, U5.4
unnamed: U5.5, U5.10
unnamed: U12.1, U15.9
unnamed: U12.4, U14.14
unnamed: U12.5, U15.6
unnamed: U12.8, U15.11
unnamed: U12.10, U14.13
unnamed: U14.2, U15.2
unnamed: U14.3, U15.15
unnamed: U25.2, U25.6
PHI0: FB39.1, U1.12, U2.1, U5.8, U19.6, U102.1
PHI2: CN1.24, U19.14, U23.27, U28.13
R_~W: CN1.5, U1.7, U2.39, U5.9, U12.3, U13.1, U22.1, U23.28, U24.7, U27.1, U28.12, U30.29, U102.38
SERIAL_RESET: U9.1, U9.3, U10.3
SID_AUDIO: R43.1, RV3.2
SND: C96.1, R8.1, U1.33
SYNC_LUM: D86.1, U1.23
VCC: C3.1, C4.1, C5.1, C6.1, C7.1, C8.1, C9.2, C21.1, C22.1, C26.2, C28.1, C29.1, C30.1, C32.1, C33.1, C34.1, C39.1, C40.1, C41.1, C42.1, C43.1, C44.1, C55.1, C56.1, C58.1, C59.1, C60.1, C61.1, C90.1, C91.1, C92.1, C94.1, C95.1, C101.1, C102.1, CN1.2, CN1.3, CN14.7, CN15.1, CN16.1, D95.1, D97.1, D99.1, F1.1, F2.1, F3.1, F4.1, F5.1, JP1.1, JP6.1, JP7.1, JP15.1, JP16.1, L1.1, Q3.2, R1.1, R3.1, R5.1, R7.1, R12.2, R14.1, R19.1, R20.1, R21.1, R23.2, R41.1, R42.1, R80.2, R93.2, R97.2, R98.1, R99.2, R102.1, RP1.1, RP2.1, RP3.1, RP4.1, RP5.1, RP7.1, RP8.1, SW1.2, TP2.1, U1.4, U2.5, U3.28, U4.28, U5.14, U6.20, U9.14, U10.4, U10.8, U12.11, U12.12, U12.14, U13.20, U14.16, U15.16, U17.16, U18.20, U19.20, U20.20, U21.14, U22.20, U23.2, U23.15, U24.25, U25.14, U26.20, U27.20, U28.20, U29.1, U29.20, U30.32, U90.14, U91.5, U92.5, U93.5, U94.5, U95.5, U102.4, U102.6, U122.22, U122.24, X1.14
VDD: C11.1, C83.1, C85.1, L1.2, Q81.2, Q82.2, Q83.2, R81.1, R86.1
VGND: C11.2, C83.2, C84.1, C85.2, C87.1, L80.2, R82.2, R83.2, R85.2, R88.2, R90.2
VSID: C51.2, C54.1, L3.2, Q6.2, TP3.1, U24.28
a0: CN1.Y, U1.3, U2.6, U3.10, U4.10, U15.4, U23.13, U24.9, U28.11, U30.7, U102.7
a1: CN1.X, U1.2, U2.7, U3.9, U4.9, U15.13, U23.14, U24.10, U28.9, U30.8, U102.8
a2: CN1.W, U1.1, U2.8, U3.8, U4.8, U15.5, U24.11, U28.8, U30.9, U102.9
a3: CN1.V, U1.48, U2.9, U3.7, U4.7, U15.12, U24.12, U28.7, U30.10, U102.10
a4: CN1.U, U1.47, U2.10, U3.6, U4.6, U19.5, U24.13, U28.6, U30.6, U102.11
a5: CN1.T, U1.46, U2.11, U3.5, U4.5, U19.4, U28.5, U30.5, U102.12
a6: CN1.S, U1.45, U2.12, U3.4, U4.4, U19.3, U28.4, U30.4, U102.13
a7: CN1.R, U1.44, U2.13, U3.3, U4.3, U19.2, U28.3, U30.3, U102.14
a8: CN1.P, U1.43, U2.14, U3.25, U4.25, U19.11, U28.2, U30.2, U102.15
a9: CN1.N, U1.42, U2.15, U3.24, U4.24, U19.8, U28.1, U30.1, U102.16
a10: CN1.M, D80.1, U1.41, U2.16, U3.21, U4.21, U30.26, U102.17
a11: CN1.L, D81.1, U1.40, U2.17, U3.23, U4.23, U30.23, U102.18
a12: CN1.K, D82.1, U1.39, U2.18, U3.2, U4.2, U26.4, U30.27, U102.19
a13: CN1.J, D83.1, U1.38, U2.19, U3.26, U4.26, U26.3, U30.25, U102.20
a14: CN1.H, D84.1, U1.37, U2.21, U26.2, U30.11, U102.22
a15: CN1.F, D85.1, U1.36, U2.22, U26.1, U30.12, U102.23
d0: CN1.21, U1.25, U2.38, U3.11, U4.11, U6.2, U13.18, U20.18, U22.18, U23.18, U24.15, U27.18, U29.18, U30.21, U102.37, U122.20
d1: CN1.20, U1.26, U2.37, U3.12, U4.12, U6.3, U13.17, U20.17, U22.17, U23.19, U24.16, U26.13, U27.17, U29.17, U30.13, U102.36, U122.19
d2: CN1.19, U1.27, U2.36, U3.13, U4.13, U6.4, U13.16, U20.3, U22.16, U23.20, U24.17, U26.12, U27.16, U29.16, U30.20, U102.35, U122.18
d3: CN1.18, U1.28, U2.35, U3.15, U4.15, U6.5, U13.15, U20.4, U22.15, U23.21, U24.18, U27.15, U29.15, U30.14, U102.34, U122.17
d4: CN1.17, U1.29, U2.34, U3.16, U4.16, U6.6, U13.14, U20.14, U22.14, U23.22, U24.19, U27.14, U29.14, U30.19, U102.33, U122.16
d5: CN1.16, U1.30, U2.33, U3.17, U4.17, U6.7, U13.13, U20.13, U22.13, U23.23, U24.20, U27.13, U29.13, U30.15, U102.32, U122.15
d6: CN1.15, U1.31, U2.32, U3.18, U4.18, U6.8, U13.12, U20.7, U22.12, U23.24, U24.21, U27.12, U29.12, U30.18, U102.31, U122.14
d7: CN1.14, U1.32, U2.31, U3.19, U4.19, U6.9, U13.11, U20.8, U22.11, U23.25, U24.22, U27.11, U29.11, U30.17, U102.30, U122.13
k0: D1.2, D7.2, FB49.1, U1.15
k1: D2.2, D8.2, FB50.1, U1.16
k2: D3.2, D9.2, FB51.1, U1.17
k3: D4.2, D10.2, FB52.1, U1.18
k4: FB53.1, U1.19
k5: FB54.1, U1.20
k6: D5.2, D12.2, FB55.1, U1.21
k7: D6.2, D11.2, FB56.1, U1.22
p0: U2.30, U9.13, U102.26
p1: U2.29, U9.11, U102.28
p2: U2.28, U9.9, U102.27
p3: D93.2, R93.1, U2.27, U9.5
p4: C23.2, D94.1, D95.2, FB16.2, U2.26, U102.25
p6: D96.1, D97.2, FB4.2, R29.2, RP1.3, U2.25, U9.10, U102.24
p7: D98.1, D99.2, FB3.2, JP12.3, RP1.4, U2.24, U9.12, U102.29
r0: RP7.2, U6.19, U26.5, U29.2
r1: RP7.3, U6.18, U26.6, U29.3
r2: RP7.4, U6.17, U26.7, U29.4
r3: RP7.5, U6.16, U29.5
r4: RP7.6, U6.15, U29.6
r5: RP7.7, U6.14, U29.7
r6: RP7.8, U6.13, U26.8, U29.8
r7: RP7.9, U6.12, U26.9, U29.9
~ACIA: U19.12, U23.3
~ATTN: FB5.2, FB63.2, RP1.2, U9.8
~BASIC_CS1: JP8.1, U14.4, U90.1
~CAS: FB40.1, U1.11, U5.6
~CASSETTE: U22.19, U28.18
~CS0: CN1.10, U1.5, U14.1
~CS1: CN1.9, U1.6, U14.15
~CS_RAMRD: U28.17, U29.19
~FUNCHI_CS: U14.11, U90.9
~FUNCLO_CS: U14.5, U90.5, U90.10
~IRQ: CN1.4, R19.2, U1.8, U2.3, U23.26, U102.3
~JOY1: U17.1, U18.1, U26.16
~JOY2: U17.15, U18.19, U26.15
~JOY3: U19.15, U27.19
~JOYSWAP: JP17.2, R97.1, U17.2, U17.14, U26.14
~KERNAL_CS1: JP5.1, U14.12, U90.2, U90.4
~RAS: FB38.1, U1.10, U19.9
~RESET: CN1.C, FB62.2, JP3.1, JP15.3, JP16.3, RP1.5, U2.40, U9.2, U15.1, U20.1, U23.4, U24.5, U25.10, U102.40
~SID: TP6.1, U19.13, U24.8
~TAPE_SENSE_USERPORT: CN10.4, JP12.1, RP4.4, U22.4, U122.6
